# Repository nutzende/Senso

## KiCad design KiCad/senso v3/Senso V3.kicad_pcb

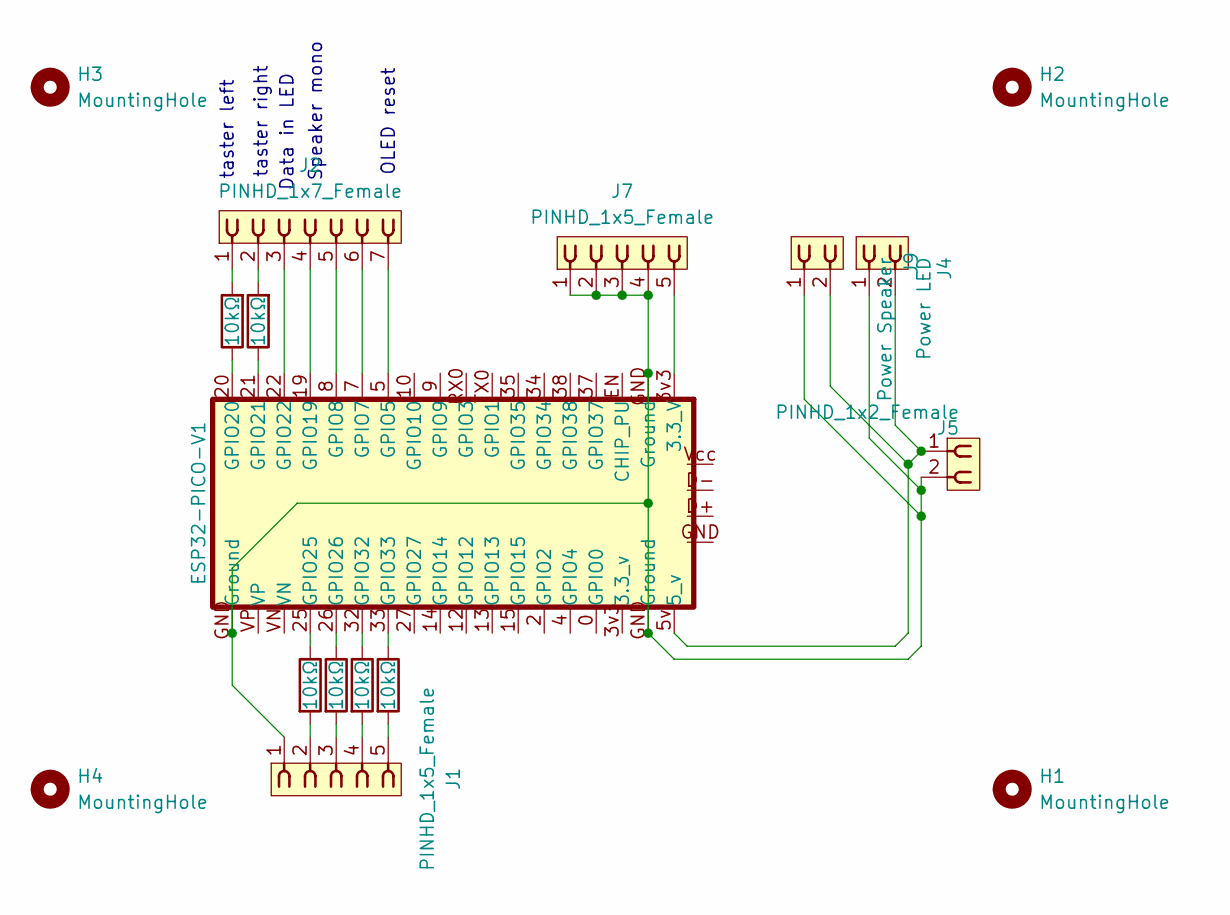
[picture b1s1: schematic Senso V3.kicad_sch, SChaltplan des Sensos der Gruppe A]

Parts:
ESP32-PICO-V1: ESP32-PICO-V3; ESP32 pico v1
H1, H2, H3, H4: MountingHole; MountingHole_3.2mm_M3
J1, J7: PINHD_1x5_Female; PinSocket_1x05_P2.54mm_Vertical
J2: PINHD_1x7_Female; PinSocket_1x07_P2.54mm_Vertical
J4: Power LED; PinSocket_1x02_P2.54mm_Vertical
J5: PINHD_1x2_Female; PinSocket_1x02_P2.54mm_Vertical
J9: Power Speaker; PinSocket_1x02_P2.54mm_Vertical
R1, R2, R5, R6, R7, R8: 10kΩ; Resistore

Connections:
unnamed: ESP32-PICO-V1.3v3 (3.3_V), J7.5
unnamed: ESP32-PICO-V1.5v (5_v), J4.2, J5.1, J9.2
unnamed: ESP32-PICO-V1.5 (GPIO5), J2.7
unnamed: ESP32-PICO-V1.7 (GPIO7), J2.6
unnamed: ESP32-PICO-V1.8 (GPIO8), J2.5
unnamed: ESP32-PICO-V1.19 (GPIO19), J2.4
unnamed: ESP32-PICO-V1.20 (GPIO20), R2.1
unnamed: ESP32-PICO-V1.21 (GPIO21), R1.1
unnamed: ESP32-PICO-V1.22 (GPIO22), J2.3
unnamed: ESP32-PICO-V1.25 (GPIO25), R5.1
unnamed: ESP32-PICO-V1.26 (GPIO26), R6.1
unnamed: ESP32-PICO-V1.32 (GPIO32), R7.1
unnamed: ESP32-PICO-V1.33 (GPIO33), R8.1
unnamed: ESP32-PICO-V1.GND (Ground), J1.1, J4.1, J5.2, J7.1, J7.2, J7.3, J7.4, J9.1
unnamed: J1.2, R5.2
unnamed: J1.3, R6.2
unnamed: J1.4, R7.2
unnamed: J1.5, R8.2
unnamed: J2.1, R2.2
unnamed: J2.2, R1.2

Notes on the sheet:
Speaker mono
OLED reset
taster right
Data in LED
taster left

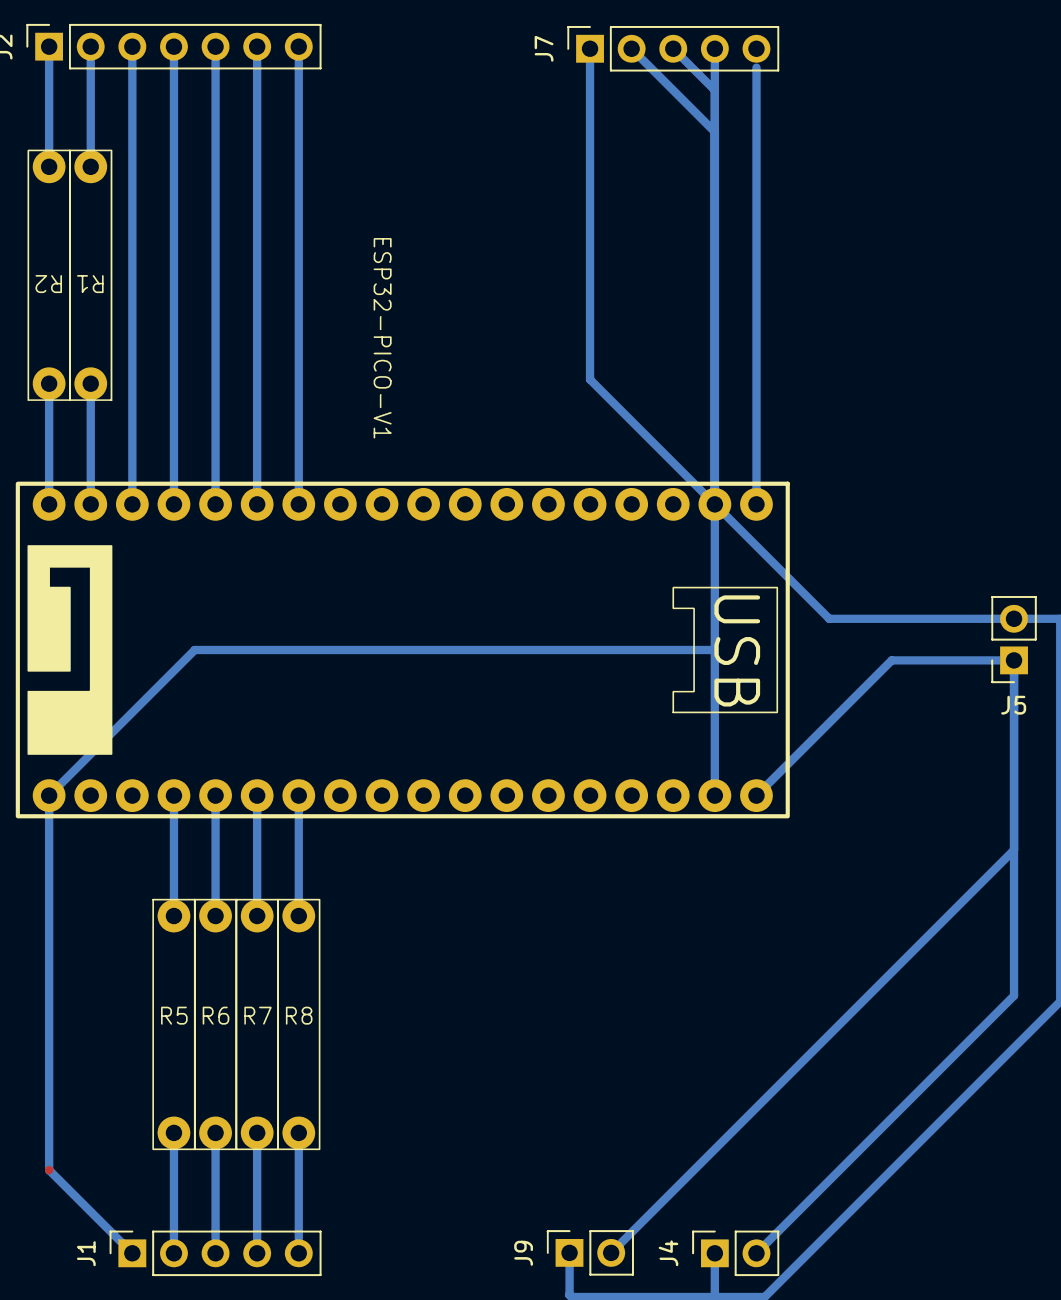
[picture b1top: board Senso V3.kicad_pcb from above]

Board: 2 copper layers, 17 parts (0 on the bottom side), 20 nets.

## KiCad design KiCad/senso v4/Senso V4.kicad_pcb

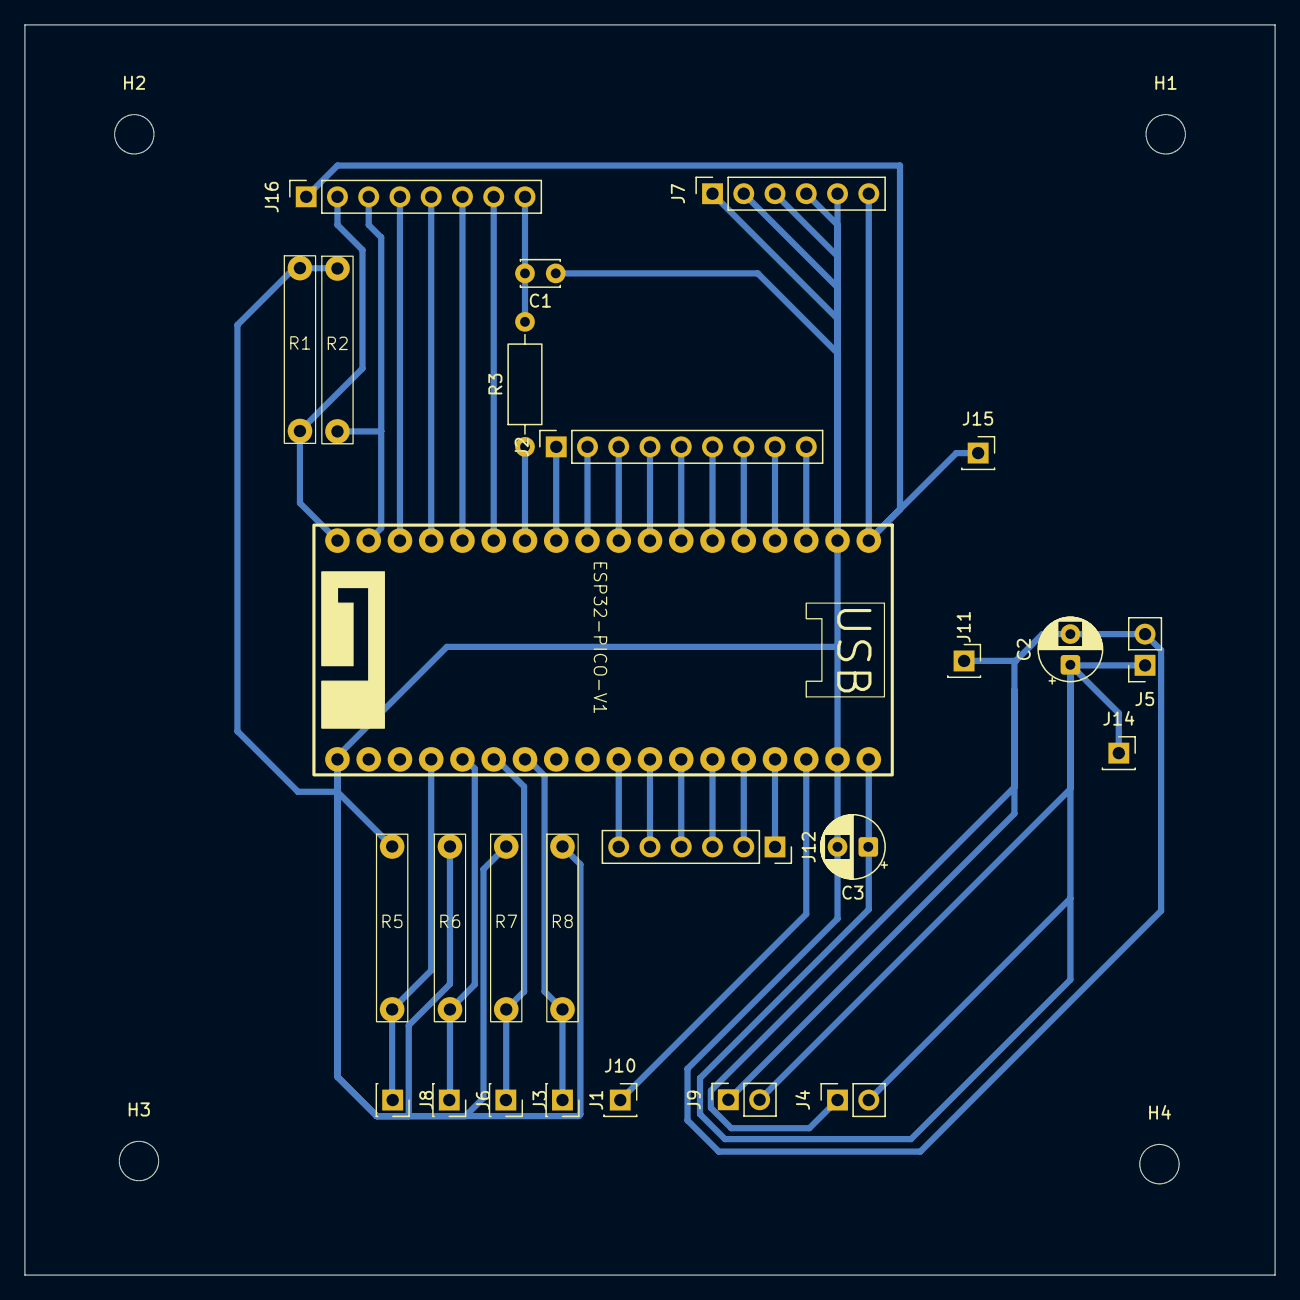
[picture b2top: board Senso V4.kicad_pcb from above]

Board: 2 copper layers, 101.6 x 101.6 mm, 30 parts (0 on the bottom side), 30 nets.

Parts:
C1: Capacitor_NP; C_Disc_D3.0mm_W2.0mm_P2.50mm
C2, C3: Capacitor_PO; CP_Radial_D5.0mm_P2.50mm
ESP32-PICO-V1: ESP32-PICO-V3; ESP32 pico v1
H1, H2, H3, H4: MountingHole; MountingHole_3.2mm_M3
J1, J3, J6, J8, J10, J11, J14, J15: PINHD_1x1_Female; PinSocket_1x01_P2.54mm_Vertical
J2: PINHD_1x9_Female; PinSocket_1x09_P2.54mm_Vertical
J4: Power LED; PinSocket_1x02_P2.54mm_Vertical
J5: PINHD_1x2_Female; PinSocket_1x02_P2.54mm_Vertical
J7, J12: PINHD_1x6_Female; PinSocket_1x06_P2.54mm_Vertical
J9: Power Speaker; PinSocket_1x02_P2.54mm_Vertical
J16: PINHD_1x8_Female; PinSocket_1x08_P2.54mm_Vertical
R1, R2, R5, R6, R7, R8: 10kΩ; Resistore
R3: 80Ω; R_Axial_DIN0207_L6.3mm_D2.5mm_P10.16mm_Horizontal

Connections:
unnamed: C1.2, J16.8, R3.2
unnamed: C2.1, C3.1, ESP32-PICO-V1.5V, J5.1, J9.2, J14.1
unnamed: ESP32-PICO-V1.EN (CHIP_PU), J2.9
unnamed: ESP32-PICO-V1.0 (GPIO0), J12.1
unnamed: ESP32-PICO-V1.TX0 (GPIO1), J2.4
unnamed: ESP32-PICO-V1.2 (GPIO2), J12.3
unnamed: ESP32-PICO-V1.RX0 (GPIO3), J2.3
unnamed: ESP32-PICO-V1.4 (GPIO4), J12.2
unnamed: ESP32-PICO-V1.5 (GPIO5), R3.1
unnamed: ESP32-PICO-V1.7 (GPIO7), J16.7
unnamed: ESP32-PICO-V1.8 (GPIO8), J16.6
unnamed: ESP32-PICO-V1.9 (GPIO9), J2.2
unnamed: ESP32-PICO-V1.10 (GPIO10), J2.1
unnamed: ESP32-PICO-V1.12 (GPIO12), J12.6
unnamed: ESP32-PICO-V1.13 (GPIO13), J12.5
unnamed: ESP32-PICO-V1.15 (GPIO15), J12.4
unnamed: ESP32-PICO-V1.19 (GPIO19), J16.5
unnamed: ESP32-PICO-V1.20 (GPIO20), J16.2, R1.2
unnamed: ESP32-PICO-V1.21 (GPIO21), J16.3, R2.2
unnamed: ESP32-PICO-V1.22 (GPIO22), J16.4
unnamed: ESP32-PICO-V1.25 (GPIO25), J8.1, R5.2
unnamed: ESP32-PICO-V1.26 (GPIO26), J6.1, R6.2
unnamed: ESP32-PICO-V1.32 (GPIO32), J3.1, R7.2
unnamed: ESP32-PICO-V1.33 (GPIO33), J1.1, R8.2
unnamed: ESP32-PICO-V1.34 (GPIO34), J2.6
unnamed: ESP32-PICO-V1.35 (GPIO35), J2.5
unnamed: ESP32-PICO-V1.37 (GPIO37), J2.8
unnamed: ESP32-PICO-V1.38 (GPIO38), J2.7
unnamed: C1.1, C2.2, C3.2, ESP32-PICO-V1.GND (Ground), J4.1, J5.2, J7.1, J7.2, J7.3, J7.4, J7.5, J9.1, J11.1, R1.1, R2.1, R5.1, R6.1, R7.1, R8.1
unnamed: ESP32-PICO-V1.3v3, J7.6, J15.1, J16.1

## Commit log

2025-10-27 init commit
    copy paste
2025-10-27 menu rename
2025-10-27 Senso Skill Level 1,2,3,4
2025-10-27 updated pin vars test.py
2025-10-27 Menüführung für Senso V1
2025-10-27 Menüführung für Senso V1.1
2025-10-27 Menüführung für Senso 1.2
2025-10-28 Updated design
2025-10-28 test
2025-10-28 remove test.md
2025-10-28 moved to folders
2025-10-30 test2
2025-10-30 Flaschendrehen + Menü Update
2025-10-30 add neopixel libary
2025-10-30 Update game_flaschendrehen.py
    optimize Flaschendrehen
2025-10-30 add Neopixel lib + test code
2025-10-30 update neopixel test code
2025-11-06 Update game_senso.py
    remove old todo
2025-11-06 difficulty in new py
2025-11-06 zwischenstand
2025-11-06 Update and rename code/difficulty.py to skilllevel.py
    Versuch des Hinzufügens des Codes aus Menu.py
    Datei trägt nun den gleichen Namen wie die in ihr enthaltene Funktion
2025-11-07 Revert "Update and rename code/difficulty.py to skilllevel.py"
    This reverts commit 6652834937da0e2c1b05195b031b4b83574c8bfa.
2025-11-07 rename difficulty.py to skilllevel.py add function number_of_players in number_of_players.py
2025-11-07 Update game_senso.py
    replace difficulty with skilllevel
2025-11-07 add game over animation
2025-11-07 add sprites
2025-11-07 Revert "add sprites"
    This reverts commit e24721be22d9c8ecce961e447d0d861c7d49909e.
2025-11-07 Revert "Revert "add sprites""
    This reverts commit 582ab5bea3b5e6a447f884e9d921456b2bc16043.
2025-11-09 add button state
2025-11-10 remove old sprite
2025-11-10 add new sprite
2025-11-10 relocate new sprites
2025-11-10 add gif
2025-11-11 add ui.bmp
2025-11-11 fix UI.bmp
2025-11-11 update assets
2025-11-11 add menu ui
2025-11-11 add whacamole + remake menu ui
2025-11-11 menu func remake for new ui
2025-11-11 add Gfx libary
2025-11-11 ui lines with gfx + simple bitmaps
2025-11-13 ui position changes
2025-11-13 finished ui
2025-11-13 text update + neopixel test
2025-11-14 i dont know
2025-11-14 Senso UI Update
2025-11-14 Neuste 3D-Modelle
2025-11-14 senso lower key state times
2025-11-14 Flaschendrehen mit Displaytexten
2025-11-14 Bilder vom Modell
2025-11-14 3d Model sortieren
2025-11-14 Noch mehr Tolle Dinge wie Doku und Modelle
2025-11-14 reaname
2025-11-14 Key switches test
2025-11-18 libary rework: rem ssd1306, gfx add ssd1309
2025-11-18 add whacamole to menu
2025-11-18 add KiCad
2025-11-18 update senso v2
2025-11-18 update KiCad
2025-11-20 add game reaction + small fixes
2025-11-20 reaction fix
2025-11-21 LED Diode -> Neopixel
2025-11-21 3D-Druck und Lasercut Datein
2025-11-21 Bilder
2025-11-21 Schaltplan
2025-11-21 Schaltplan 2
2025-11-21 Wochenbericht
2025-11-23 add everything back in
2025-11-23 add KiCadv3
2025-11-24 menu ui update
2025-11-25 Startup Animation + Neopixel Update
2025-11-26 add progressbar
2025-11-26 add Gamemode Senso Choose Color
2025-11-26 add Gamemode Senso player adds
2025-11-26 removed old filed
2025-11-26 reaction game finished
2025-11-26 progressbar range limits
2025-11-26 buttons und leds an menu ui angepasst
2025-11-27 remove KiCad
2025-11-27 cleanup
2025-11-27 Blender
2025-11-27 WerbeFilm Neu
2025-11-27 pinout platine
2025-11-27 Zwischenstand Late Night Sprint
2025-11-27 WerbeFilm V3
2025-11-27 switch buttons and led for menu ui
2025-11-27 WerbeFilm + Model
2025-11-27 ganz viele Modelle
2025-11-27 Render Bild
2025-11-27 Senso Mit Pfeilen
2025-11-27 Pfeile
2025-11-27 datein ::)))))
2025-11-27 bugfixes
2025-11-27 Sortierung
2025-11-27 Datein
2025-11-27 add reset pin
2025-11-27 Platine
2025-11-27 progress in senso
2025-11-28 Create LICENSE
